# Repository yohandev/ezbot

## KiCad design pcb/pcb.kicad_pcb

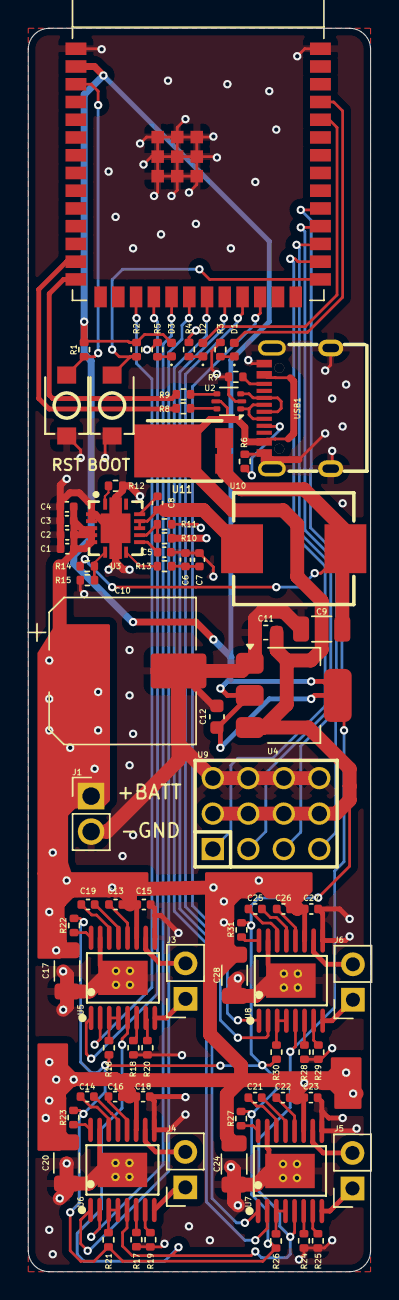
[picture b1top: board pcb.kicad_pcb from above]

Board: 4 copper layers, 24.5 x 89.0 mm, 81 parts (0 on the bottom side), 76 nets.

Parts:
BOOT: TS-1088-AR02016; SW-SMD_L3.9-W3.0-P4.45
C1, C2, C3, C4: 4.7µF 1mΩ; C_0402_1005Metric
C5: 2.2nF 0Ω; C_0402_1005Metric
C6: 6.8nF; C_0402_1005Metric
C7: 68pF; C_0402_1005Metric
C8: 100nF; C_0402_1005Metric
C9: 47µF 3mΩ; C_1206_3216Metric
C10: 220µF; CP_Elec_10x10
C11, C12: 22µF 16V; C_0603_1608Metric
C13, C15, C16, C18, C22, C23, C26, C27: 0.1µF; C_0402_1005Metric
C14, C19, C21, C25: 0.022µF; C_0402_1005Metric
C17, C20, C24, C28: 100µF; C_1206_3216Metric
D1, D2, D3: LED; LED_0402_1005Metric
J1: Header Pins; PinHeader_1x02_P2.54mm_Vertical
J3, J4, J5, J6: Conn_01x02_Pin; PinSocket_1x02_P2.54mm_Vertical
R1, R2, R6, R7: 5kΩ; R_0402_1005Metric
R3, R4, R5: 1kΩ; R_0402_1005Metric
R8, R9: 0Ω; R_0402_1005Metric
R10: 102kΩ; R_0402_1005Metric
R11: 36.5kΩ; R_0402_1005Metric
R12, R14: 53.6kΩ; R_0402_1005Metric
R13: 3.92kΩ; R_0402_1005Metric
R15, R16, R21, R22, R23, R26, R27, R30, R31: 10kΩ; R_0402_1005Metric
R17, R18, R24, R28: 4.87kΩ; R_0402_1005Metric
R19, R20, R25, R29: 20kΩ; R_0402_1005Metric
RST: TS-1088-AR02016; SW-SMD_L3.9-W3.0-P4.45
U1: ESP32-S3-WROOM-1
U2: USBLC6-2P6; SOT-666
U3: TPS54620RHLR; VQFN-14_L3.5-W3.5-P0.50-TL-EP_TPS54622RHLT
U4: AMS1117-3.3; SOT-223-3_TabPin2
U5, U6, U7, U8: DRV8874PWPR; HTSSOP-16_L5.0-W4.4-P0.65-LS6.4-BL-EP
U9: 3x4; HDR-TH_12P-P2.54-V-M-R3-C4-S2.54
U10: 2.2µH 12.7mΩ; IND-SMD_L8.6-W8.0
U11: 10S45SP; TO-277_3P-L5.4-W4.0-LS6.5-TR-1
USB1: TYPE-C 16PIN 2MD(073); USB-C-SMD_TYPE-C-6PIN-2MD-073

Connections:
+3V3: C12.1, D3.2 (A), R1.1, R2.1, U1.2 (3V3), U4.2 (VO), U5.5 (VREF), U6.5 (VREF), U7.5 (VREF), U8.5 (VREF)
+5V: C11.1, R16.1, R21.1, R22.1, R23.1, R26.1, R27.1, R30.1, R31.1, U2.5 (VBUS), U4.3 (VI), U9.2, U9.5, U9.8, U9.11, U11.3 (K), USB1.2 (VBUS), USB1.11 (VBUS)
+BATT: C1.1, C2.1, C3.1, C4.1, C10.1, C13.2, C15.1, C16.2, C17.1, C18.1, C20.1, C22.2, C23.1, C24.1, C26.2, C27.1, C28.1, J1.1, R10.1, U3.4 (PVIN), U3.5 (PVIN), U3.6 (VIN), U5.11 (VM), U6.11 (VM), U7.11 (VM), U8.11 (VM)
BOOT: BOOT.2, R2.2, U1.27 (GPIO0/BOOT)
GND: BOOT.1, C1.2, C2.2, C3.2, C4.2, C5.2, C6.2, C7.2, C9.2, C10.2, C11.2, C12.2, C15.2, C17.2, C18.2, C20.2, C23.2, C24.2, C27.2, C28.2, J1.2, R3.2, R4.2, R5.2, R6.2, R7.2, R11.2, R12.2, R15.2, R17.2, R18.2, R19.2, R20.2, R24.2, R25.2, R28.2, R29.2, RST.1, U1.1 (GND), U1.40 (GND), U1.41 (GND), U2.2 (GND), U3.2 (GND), U3.3 (GND), U3.15 (EP), U4.1 (GND), U5.9 (PGND), U5.15 (GND), U5.17 (EP), U6.9 (PGND), U6.15 (GND), U6.17 (EP), U7.9 (PGND), U7.15 (GND), U7.17 (EP), U8.9 (PGND), U8.15 (GND), U8.17 (EP), U9.3, U9.6, U9.9, U9.12, USB1.1 (GND), USB1.12 (GND), USB1.13 (SHELL), USB1.14 (SHELL)
IO43: D1.2 (A), U1.37 (U0TXD/GPIO43/CLK_OUT1)
IO44: D2.2 (A), U1.36 (U0RXD/GPIO44/CLK_OUT2)
M0 EN: U1.18 (GPIO10/TOUCH10/ADC1_CH9/FSPICS0/FSPIIO4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), U5.1 (EN/IN1)
M0 PH: U1.17 (GPIO9/TOUCH9/ADC1_CH8/FSPIHD/SUBSPIHD), U5.2 (PH/IN2)
M1 EN: U1.20 (GPIO12/TOUCH12/ADC2_CH1/FSPICLK/FSPIIO6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), U6.1 (EN/IN1)
M1 PH: U1.19 (GPIO11/TOUCH11/ADC2_CH0/FSPID/FSPIIO5/S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), U6.2 (PH/IN2)
M2 EN: U1.22 (GPIO14/TOUCH14/ADC2_CH3/FSPIWP/FSPIDQS/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), U7.1 (EN/IN1)
M2 PH: U1.21 (GPIO13/TOUCH13/ADC2_CH2/FSPIQ/FSPIIO7/S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), U7.2 (PH/IN2)
M3 EN: U1.24 (GPIO47/SPICLK_P/SUBSPICLK_P_DIFF), U8.1 (EN/IN1)
M3 PH: U1.23 (GPIO21), U8.2 (PH/IN2)
unnamed: C6.1, C7.1, R13.2
unnamed: C8.1, U3.11 (PH), U3.12 (PH), U10.1
unnamed: C9.1, R14.1, U10.2, U11.1 (A), U11.2 (A)
unnamed: D1.1 (K), R3.1
unnamed: D2.1 (K), R4.1
unnamed: D3.1 (K), R5.1
unnamed: J3.1, U5.8 (OUT1)
unnamed: J3.2, U5.10 (OUT2)
unnamed: J4.1, U6.8 (OUT1)
unnamed: J4.2, U6.10 (OUT2)
unnamed: J5.1, U7.8 (OUT1)
unnamed: J5.2, U7.10 (OUT2)
unnamed: J6.1, U8.8 (OUT1)
unnamed: J6.2, U8.10 (OUT2)
unnamed: R8.1, U2.6 (I/O1)
unnamed: R9.1, U2.4 (I/O2)
unnamed: C8.2, U3.13 (BOOT)
unnamed: R13.1, U3.8 (COMP)
unnamed: R10.2, R11.1, U3.10 (EN)
unnamed: R12.1, U3.1 (RT/CLK)
unnamed: C5.1, U3.9 (SS/TR)
unnamed: R14.2, R15.1, U3.7 (VSENSE)
unnamed: C19.2, U5.13 (CPH)
unnamed: C19.1, U5.14 (CPL)
unnamed: R20.1, U5.7 (IMODE)
unnamed: R18.1, U5.6 (IPROPI)
unnamed: R22.2, U5.16 (PMODE)
unnamed: C13.1, U5.12 (VCP)
unnamed: R16.2, U5.3 (nSLEEP), U5.4 (nFAULT)
unnamed: C14.2, U6.13 (CPH)
unnamed: C14.1, U6.14 (CPL)
unnamed: R19.1, U6.7 (IMODE)
unnamed: R17.1, U6.6 (IPROPI)
unnamed: R23.2, U6.16 (PMODE)
unnamed: C16.1, U6.12 (VCP)
unnamed: R21.2, U6.3 (nSLEEP), U6.4 (nFAULT)
unnamed: C21.2, U7.13 (CPH)
unnamed: C21.1, U7.14 (CPL)
unnamed: R25.1, U7.7 (IMODE)
unnamed: R24.1, U7.6 (IPROPI)
unnamed: R27.2, U7.16 (PMODE)
unnamed: C22.1, U7.12 (VCP)
unnamed: R26.2, U7.3 (nSLEEP), U7.4 (nFAULT)
unnamed: C25.2, U8.13 (CPH)
unnamed: C25.1, U8.14 (CPL)
unnamed: R29.1, U8.7 (IMODE)
unnamed: R28.1, U8.6 (IPROPI)
unnamed: R31.2, U8.16 (PMODE)
unnamed: C26.1, U8.12 (VCP)
unnamed: R30.2, U8.3 (nSLEEP), U8.4 (nFAULT)
unnamed: R6.1, USB1.4 (CC1)
unnamed: R7.1, USB1.10 (CC2)
unnamed: U2.1 (I/O1), USB1.5 (DN2), USB1.7 (DN1)
unnamed: U2.3 (I/O2), USB1.6 (DP1), USB1.8 (DP2)
RST: R1.2, RST.2, U1.3 (EN)
S0: U1.28 (SPIIO6/GPIO35/FSPID/SUBSPID), U9.1
S1: U1.29 (SPIIO7/GPIO36/FSPICLK/SUBSPICLK), U9.4
S2: U1.30 (SPIDQS/GPIO37/FSPIQ/SUBSPIQ), U9.7
S3: U1.31 (GPIO38/FSPIWP/SUBSPIWP), U9.10
USB D+: R9.2, U1.14 (GPIO20/U1CTS/ADC2_CH9/CLK_OUT1/USB_D+)
USB D-: R8.2, U1.13 (GPIO19/U1RTS/ADC2_CH8/CLK_OUT2/USB_D-)

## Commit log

2026-03-31 Add scaffolding
2026-03-31 Add upload using webserial
2026-03-31 Make upload firmware a modal
2026-03-31 Add timeout for connecting to bootloader
2026-04-02 New approach for uploading firmware using littlefs
2026-04-02 Add `upload` package, which works both locally (node.js) and on the web (WebSerial)
2026-04-03 Add CLI for fast flashing
2026-04-03 Re-organized
2026-04-03 Demo that code splitting works
2026-04-03 Fix firmware upload
2026-04-04 Fix firmware bricked in Thonny
2026-04-04 Fix motor driver
2026-04-04 Fill in scaffolding
2026-04-04 Fix reconnection (when remote disconnects)
2026-04-04 make the UI sexy
2026-04-04 Add spnner while connecting
2026-04-04 Add WebBluetooth check
2026-04-04 Fix build script for image assets
2026-04-04 Fix placeholder CDN in CLI script
2026-04-05 Add demo bot
2026-04-07 Log when rebuilt
2026-04-07 Add servo
2026-04-08 Fix remote name not being advertised
2026-04-09 Add firmware renaming
2026-04-09 Add enclosure
2026-04-09 Reverse arcade driving
2026-04-09 Make slider touch target bigger
2026-04-09 Add yarn scripts
2026-04-09 Put motion joystick on the left
2026-04-09 Add info (1/2)
2026-04-09 Add PCB
2026-04-09 Add info (2/2)
2026-04-09 Make the collapsible info sections more obvious
2026-04-09 Fix install scripts
2026-04-09 Add clarification on servo motor
2026-04-09 Add footers
2026-04-09 Fix images when deployed
2026-04-10 Add hero video
